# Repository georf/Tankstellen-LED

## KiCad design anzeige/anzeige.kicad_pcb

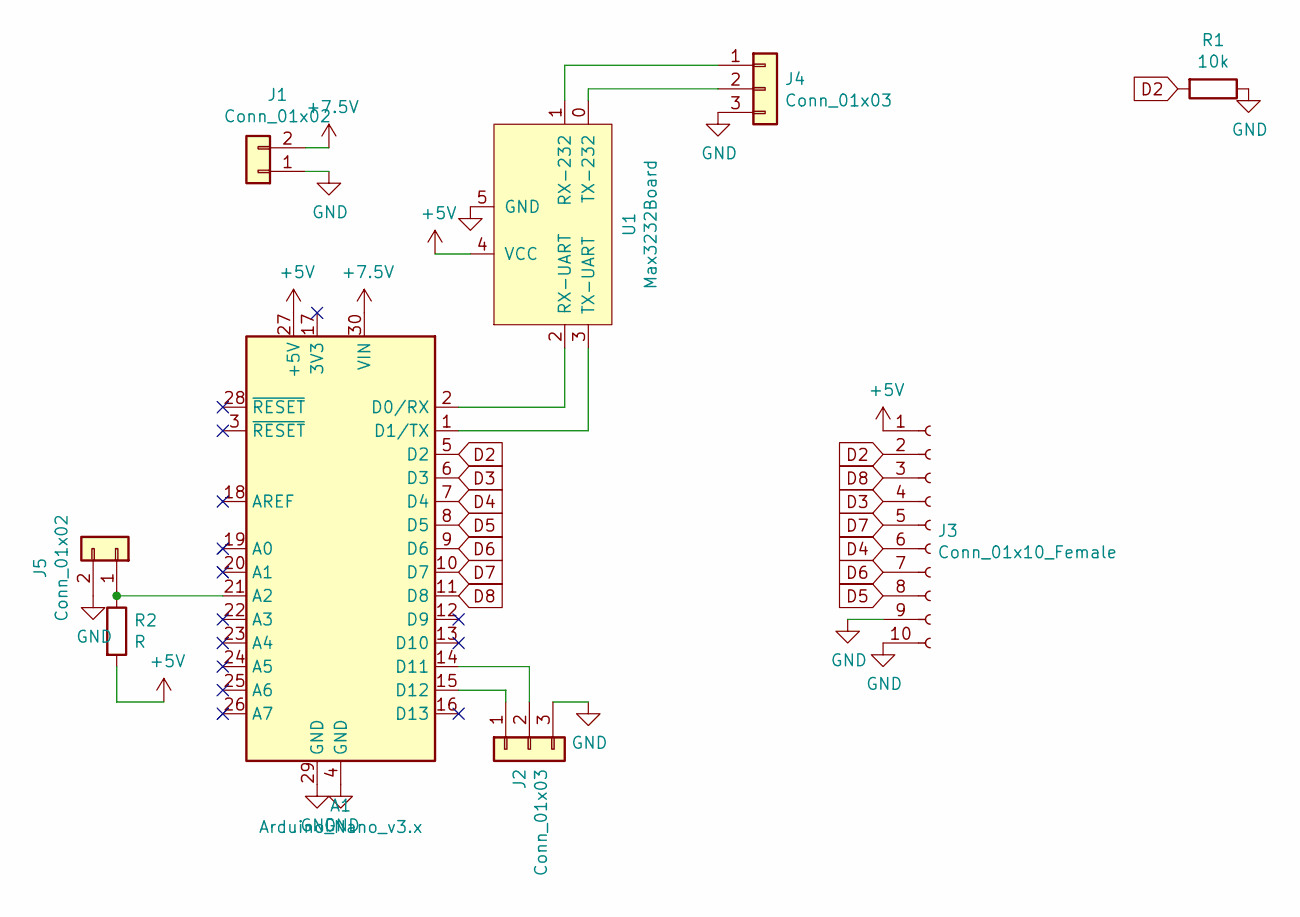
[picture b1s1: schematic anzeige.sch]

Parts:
A1: Arduino_Nano_v3.x; Arduino_Nano_longpad
J1, J5: Conn_01x02; Connector 2xPin
J2, J4: Conn_01x03; Connector 3xPin
J3: Conn_01x10_Female; IDC-Header_2x05_P2.54mm_Vertical_long_pads
R1: 10k; Resistor, L6mm,5holes
R2: R; R_Axial_DIN0204_L3.6mm_D1.6mm_P7.62mm_Horizontal
U1: Max3232Board; MAX232

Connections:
+5V: A1.27 (+5V), J3.1, R2.2, U1.4 (VCC)
+7.5V: A1.30 (VIN), J1.2
D2: A1.5 (D2), J3.2, R1.2
D3: A1.6 (D3), J3.4
D4: A1.7 (D4), J3.6
D5: A1.8 (D5), J3.8
D6: A1.9 (D6), J3.7
D7: A1.10 (D7), J3.5
D8: A1.11 (D8), J3.3
GND: A1.4 (GND), A1.29 (GND), J1.1, J2.3, J3.9, J3.10, J4.3, J5.2, R1.1, U1.5 (GND)
unnamed: A1.1 (D1/TX), U1.3 (TX-UART)
unnamed: A1.2 (D0/RX), U1.2 (RX-UART)
unnamed: A1.14 (D11), J2.2
unnamed: A1.15 (D12), J2.1
unnamed: A1.21 (A2), J5.1, R2.1
unnamed: J4.1, U1.1 (RX-232)
unnamed: J4.2, U1.0 (TX-232)

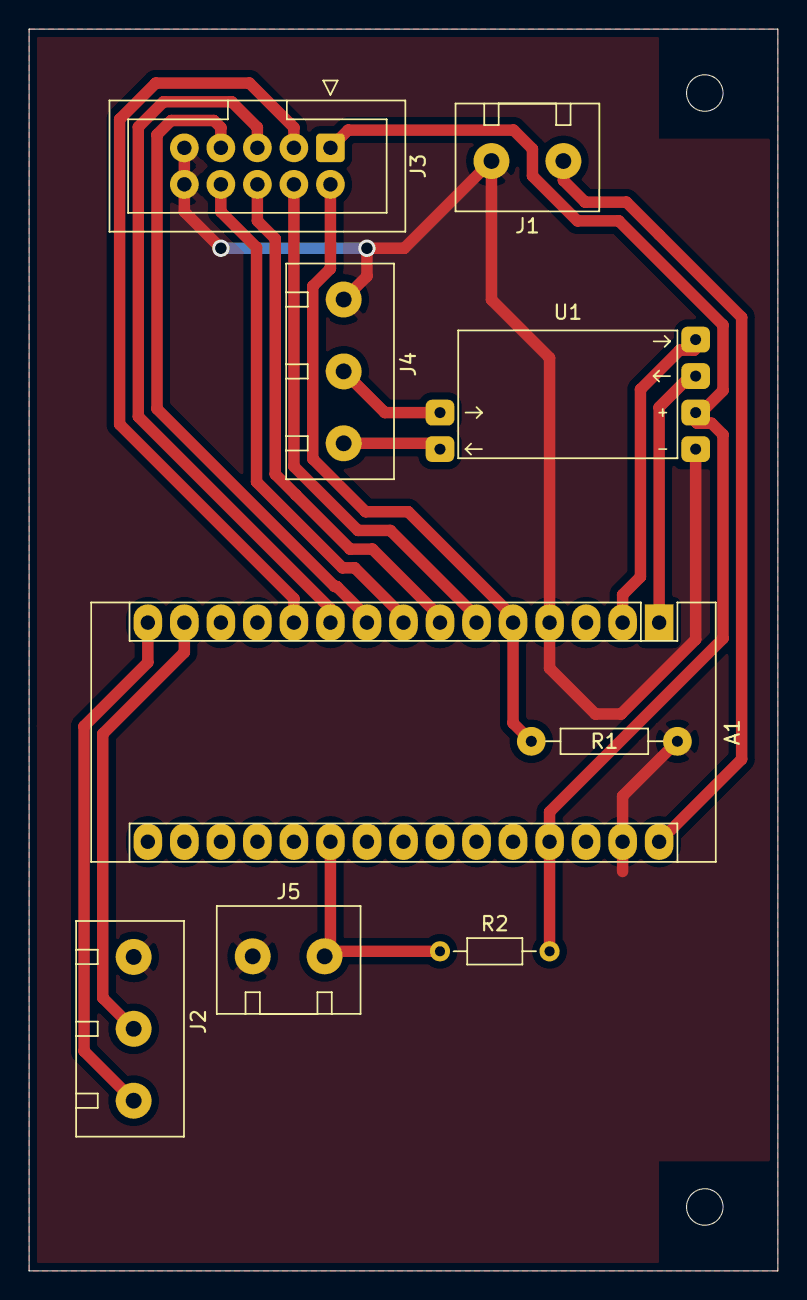
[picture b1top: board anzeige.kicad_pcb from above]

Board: 2 copper layers, 52.1 x 86.4 mm, 9 parts (0 on the bottom side), 17 nets.

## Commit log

2021-08-19 Helligkeitssteuerung
2021-08-31 Helligkeit öfter abfragen
2021-08-31 Anlage von Platz-Gamstädt über Serielle Schnittstelle ermöglichen
2021-08-31 Helligkeitsflackern minimieren
2021-08-31 Erweiterung der Platine
2021-10-09 Konvertierung der Zeiten korrigieren
